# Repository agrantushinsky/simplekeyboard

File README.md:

# simplekeyboard: 60% Mechanical Keyboard PCB
## Overview
A custom 60% mechanical keyboard 2-layer PCB built around an STM32 microcontroller and USB-C connectivity. The design utilizes I2C IO expanders to simplify matrix trace routing across the board. 

## Current Status (WIP)
Hardware bring-up is actively underway. I identified an error that swapped the SCL and SDA lines on one of the IO expanders. The next step is performing a physical trace bodge to fix the bus so I can finish validating the matrix polling logic.

## Schematics

*View the full schematic PDF: [schematics.pdf](assets/schematics.pdf)*

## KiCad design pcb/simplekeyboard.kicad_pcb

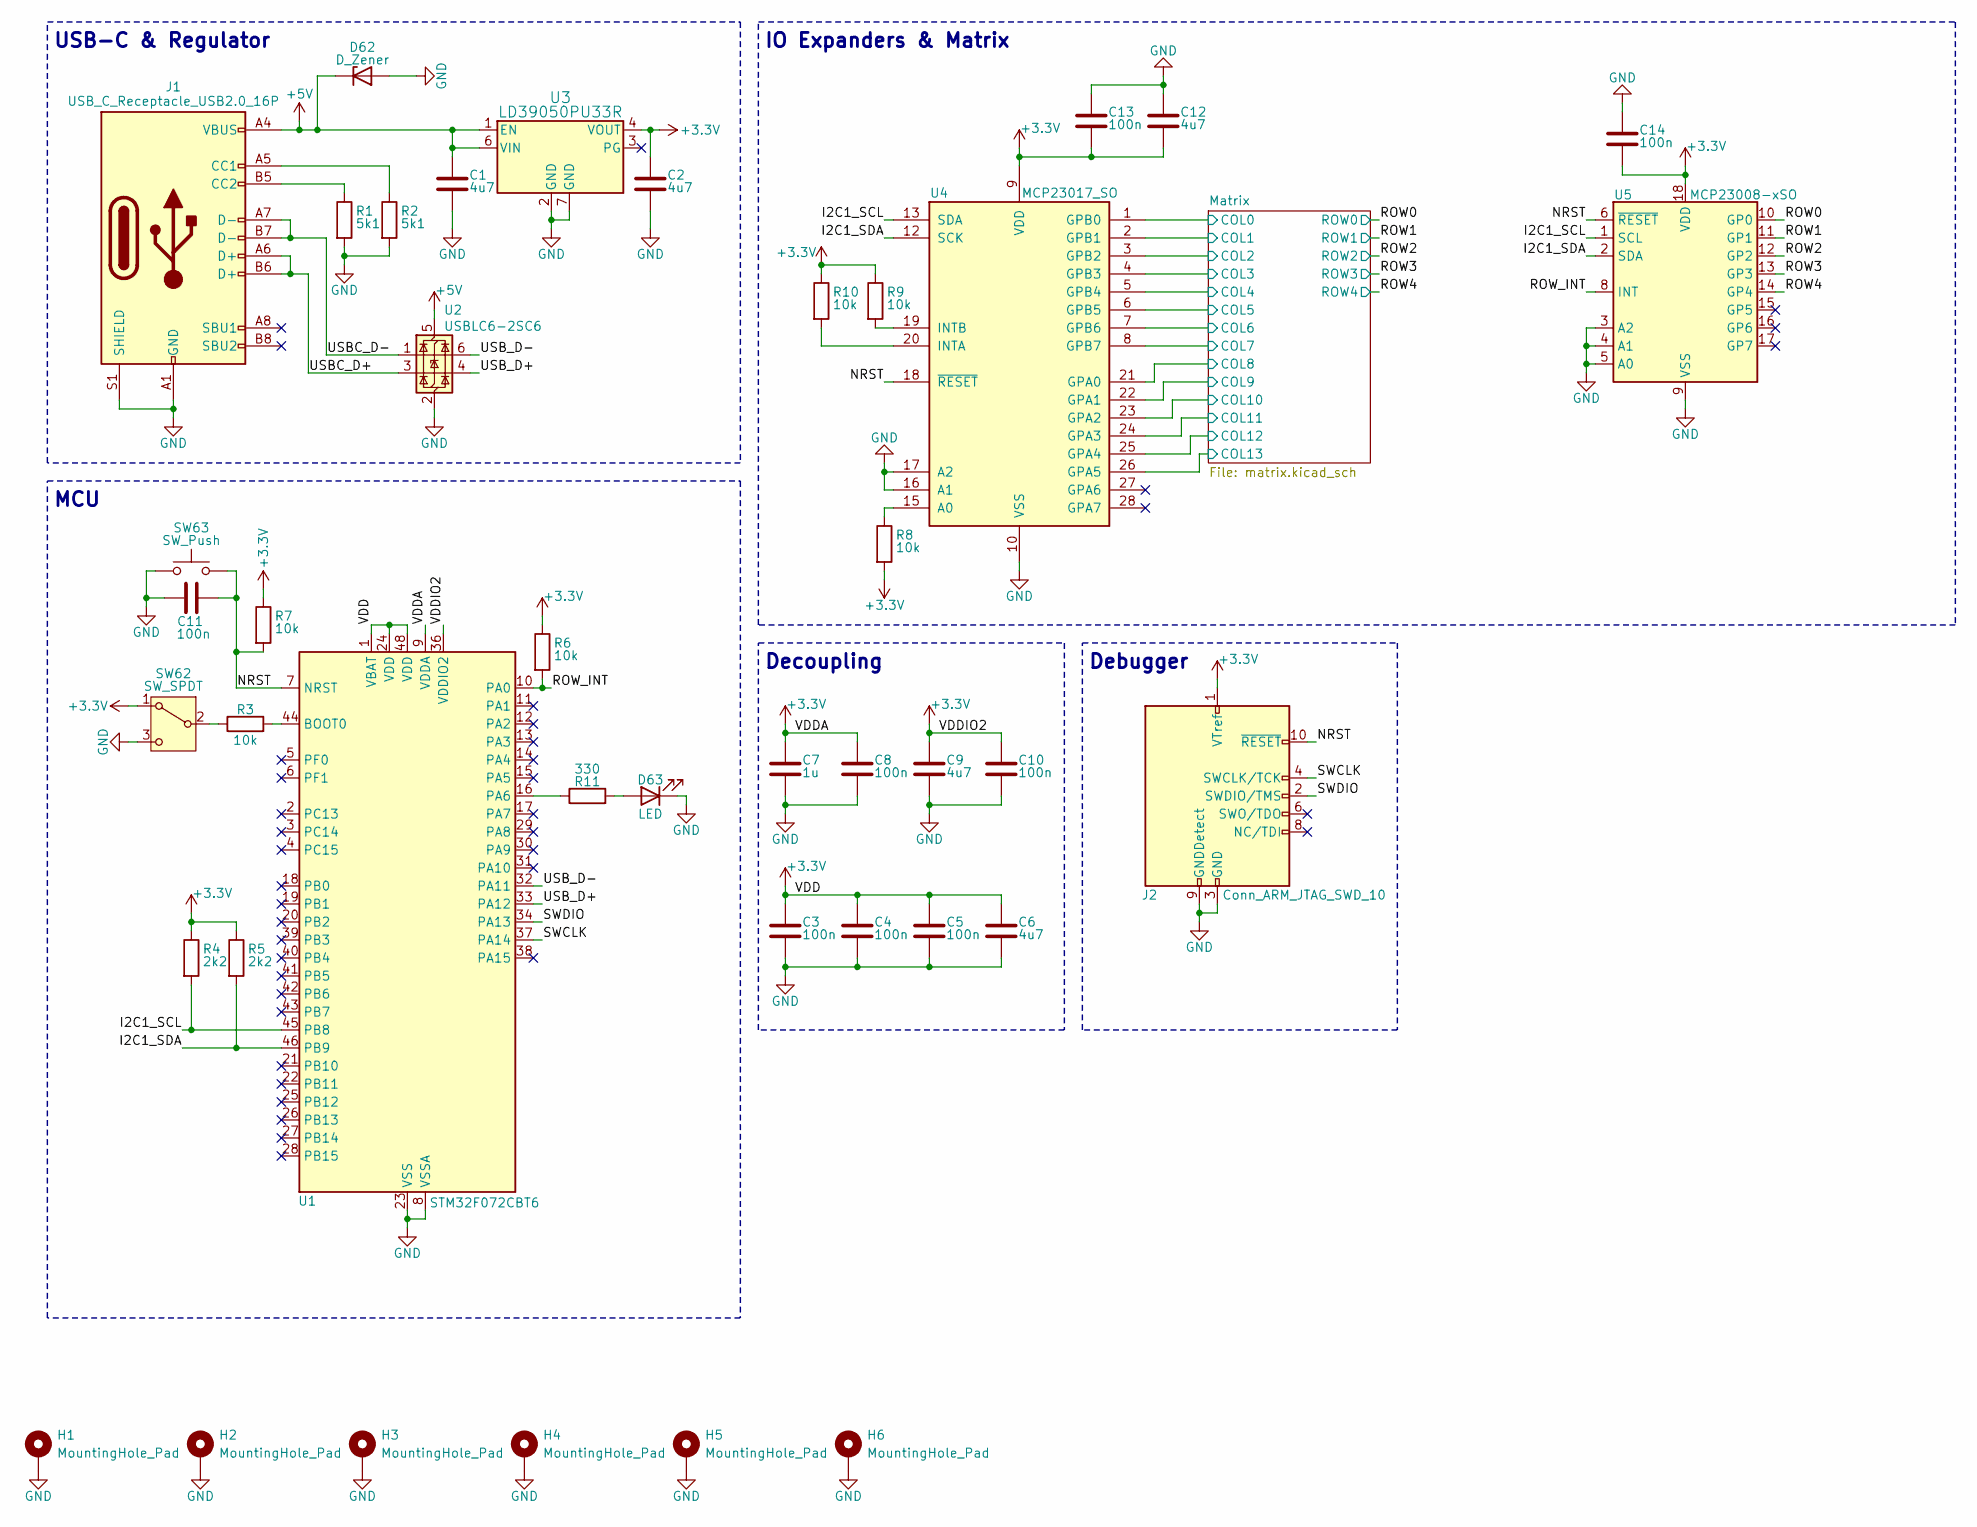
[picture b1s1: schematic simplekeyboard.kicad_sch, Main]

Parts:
C1, C2, C6, C9, C12: 4u7; C_0603_1608Metric
C3, C4, C5, C8, C10, C11, C13, C14: 100n; C_0402_1005Metric
C7: 1u; C_0603_1608Metric
D62: D_Zener; D_SOD-123
D63: LED; LED_0603_1608Metric
H1: MountingHole_Pad; 2.5mm
H2, H3, H4, H5, H6: MountingHole_Pad; 2.5mm_Oblong
J1: USB_C_Receptacle_USB2.0_16P; USB_C_Receptacle_HRO_TYPE-C-31-M-12
J2: Conn_ARM_JTAG_SWD_10; PinHeader_2x05_P1.27mm_Horizontal
R1, R2: 5k1; R_0603_1608Metric
R3, R6, R7, R8, R9, R10: 10k; R_0603_1608Metric
R4, R5: 2k2; R_0603_1608Metric
R11: 330; R_0603_1608Metric
SW62: SW_SPDT; SW_Slide_SPDT_Straight_CK_OS102011MS2Q
SW63: SW_Push; SW_PUSH_6mm
U1: STM32F072CBT6; LQFP-48_7x7mm_P0.5mm
U2: USBLC6-2SC6; SOT-23-6
U3: LD39050PU33R; DFN6_3X3_STM
U4: MCP23017_SO; SOIC-28W_7.5x17.9mm_P1.27mm
U5: MCP23008-xSO; SOIC-18W_7.5x11.6mm_P1.27mm

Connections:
+3.3V: C2.1, C3.1, C4.1, C5.1, C6.1, C7.1, C8.1, C9.1, C10.1, C12.2, C13.2, C14.2, J2.1 (VTref), R4.1, R5.1, R6.1, R7.1, R8.2, R9.1, R10.1, SW62.1 (A), U1.1 (VBAT), U1.9 (VDDA), U1.24 (VDD), U1.36 (VDDIO2), U1.48 (VDD), U3.4 (VOUT), U4.9 (VDD), U5.18 (VDD)
+5V: C1.1, D62.1 (K), J1.A4 (VBUS), J1.A9 (VBUS), J1.B4 (VBUS), J1.B9 (VBUS), U2.5 (VBUS), U3.1 (EN), U3.6 (VIN)
/I2C1_SCL: R4.2, U1.45 (PB8), U4.13 (SDA), U5.1 (SCL)
/I2C1_SDA: R5.2, U1.46 (PB9), U4.12 (SCK), U5.2 (SDA)
/Matrix/COL0: U4.1 (GPB0); also elsewhere on the board
/Matrix/COL1: U4.2 (GPB1); also elsewhere on the board
/Matrix/COL2: U4.3 (GPB2); also elsewhere on the board
/Matrix/COL3: U4.4 (GPB3); also elsewhere on the board
/Matrix/COL4: U4.5 (GPB4); also elsewhere on the board
/Matrix/COL5: U4.6 (GPB5); also elsewhere on the board
/Matrix/COL6: U4.7 (GPB6); also elsewhere on the board
/Matrix/COL7: U4.8 (GPB7); also elsewhere on the board
/Matrix/COL8: U4.21 (GPA0); also elsewhere on the board
/Matrix/COL9: U4.22 (GPA1); also elsewhere on the board
/Matrix/COL10: U4.23 (GPA2); also elsewhere on the board
/Matrix/COL11: U4.24 (GPA3); also elsewhere on the board
/Matrix/COL12: U4.25 (GPA4); also elsewhere on the board
/Matrix/COL13: U4.26 (GPA5); also elsewhere on the board
/NRST: C11.2, J2.10 (~RESET), R7.2, SW63.2, U1.7 (NRST), U4.18 (~RESET), U5.6 (~RESET)
/ROW0: U5.10 (GP0); also elsewhere on the board
/ROW1: U5.11 (GP1); also elsewhere on the board
/ROW2: U5.12 (GP2); also elsewhere on the board
/ROW3: U5.13 (GP3); also elsewhere on the board
/ROW4: U5.14 (GP4); also elsewhere on the board
/ROW_INT: R6.2, U1.10 (PA0), U5.8 (INT)
/SWCLK: J2.4 (SWCLK/TCK), U1.37 (PA14)
/SWDIO: J2.2 (SWDIO/TMS), U1.34 (PA13)
/USBC_D+: J1.A6 (D+), J1.B6 (D+), U2.3 (I/O2)
/USBC_D-: J1.A7 (D-), J1.B7 (D-), U2.1 (I/O1)
/USB_D+: U1.33 (PA12), U2.4 (I/O2)
/USB_D-: U1.32 (PA11), U2.6 (I/O1)
GND: C1.2, C2.2, C3.2, C4.2, C5.2, C6.2, C7.2, C8.2, C9.2, C10.2, C11.1, C12.1, C13.1, C14.1, D62.2 (A), D63.1 (K), H1.1, H2.1, H3.1, H4.1, H5.1, H6.1, J1.A1 (GND), J1.A12 (GND), J1.B1 (GND), J1.B12 (GND), J1.S1 (SHIELD), J2.3 (GND), J2.5 (GND), J2.9 (GNDDetect), R1.2, R2.2, SW62.3 (C), SW63.1, U1.8 (VSSA), U1.23 (VSS), U1.35 (VSS), U1.47 (VSS), U2.2 (GND), U3.2 (GND), U3.7 (GND), U4.10 (VSS), U4.16 (A1), U4.17 (A2), U5.3 (A2), U5.4 (A1), U5.5 (A0), U5.9 (VSS)
unnamed: D63.2 (A), R11.2
unnamed: J1.A5 (CC1), R2.1
unnamed: J1.B5 (CC2), R1.1
unnamed: R3.1, SW62.2 (B)
unnamed: R3.2, U1.44 (BOOT0)
unnamed: R11.1, U1.16 (PA6)
unnamed: R8.1, U4.15 (A0)
unnamed: R10.2, U4.20 (INTA)
unnamed: R9.2, U4.19 (INTB)

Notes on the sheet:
Decoupling
MCU
IO Expanders & Matrix
USB-C & Regulator
Debugger

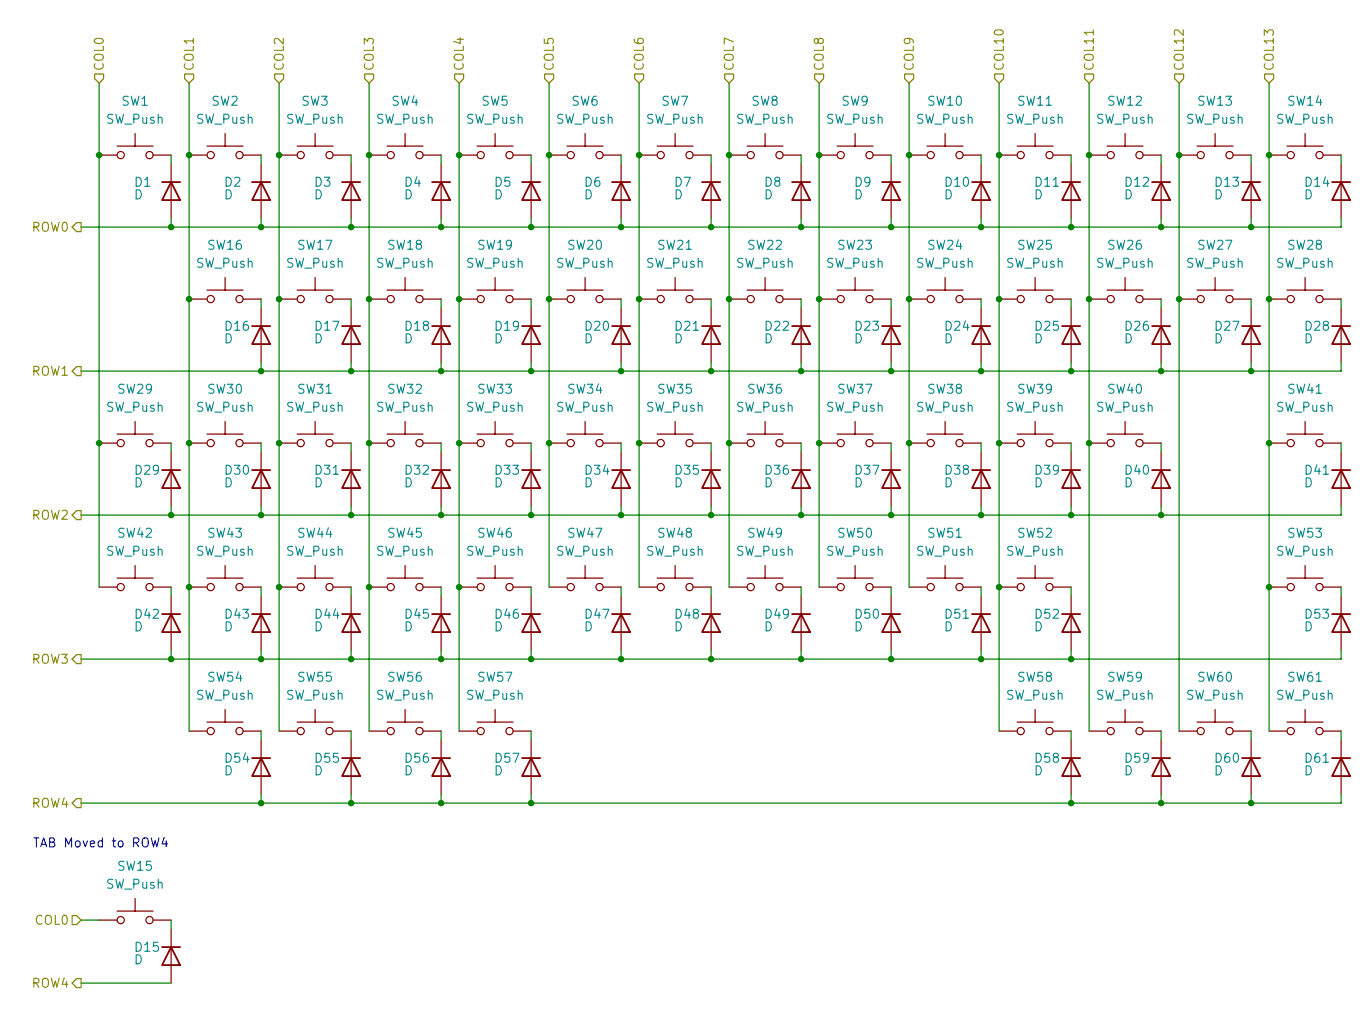
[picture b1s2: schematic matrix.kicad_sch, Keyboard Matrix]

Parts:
D1, D2, D3, D4, D5, D6, D7, D8, D9, D10, D11, D12, D13, D14, D15, D16, D17, D18, D19, D20, D21, D22, D23, D24, D25, D26, D27, D28, D29, D30, D31, D32, D33, D34, D35, D36, D37, D38, D39, D40, D41, D42, D43, D44, D45, D46, D47, D48, D49, D50, D51, D52, D53, D54, D55, D56, D57, D58, D59, D60, D61: D; D_SOD-123
SW1, SW2, SW3, SW4, SW5, SW6, SW7, SW8, SW9, SW10, SW11, SW12, SW13, SW16, SW17, SW18, SW19, SW20, SW21, SW22, SW23, SW24, SW25, SW26, SW27, SW30, SW31, SW32, SW33, SW34, SW35, SW36, SW37, SW38, SW39, SW40, SW43, SW44, SW45, SW46, SW47, SW48, SW49, SW50, SW51, SW52: SW_Push; MX-Solderable-1U
SW14: SW_Push; MX-Solderable-2U
SW15, SW28: SW_Push; MX-Solderable-1.5U
SW29: SW_Push; MX-Solderable-1.75U
SW41, SW42: SW_Push; MX-Solderable-2.25U
SW53: SW_Push; MX-Solderable-2.75U
SW54, SW55, SW56, SW58, SW59, SW60, SW61: SW_Push; MX-Solderable-1.25U
SW57: SW_Push; MX-Solderable-6.25U-ReversedStabilizers

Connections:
/Matrix/COL0: SW1.1, SW15.1, SW29.1, SW42.1; also elsewhere on the board
/Matrix/COL1: SW2.1, SW16.1, SW30.1, SW43.1, SW54.1; also elsewhere on the board
/Matrix/COL2: SW3.1, SW17.1, SW31.1, SW44.1, SW55.1; also elsewhere on the board
/Matrix/COL3: SW4.1, SW18.1, SW32.1, SW45.1, SW56.1; also elsewhere on the board
/Matrix/COL4: SW5.1, SW19.1, SW33.1, SW46.1, SW57.1; also elsewhere on the board
/Matrix/COL5: SW6.1, SW20.1, SW34.1, SW47.1; also elsewhere on the board
/Matrix/COL6: SW7.1, SW21.1, SW35.1, SW48.1; also elsewhere on the board
/Matrix/COL7: SW8.1, SW22.1, SW36.1, SW49.1; also elsewhere on the board
/Matrix/COL8: SW9.1, SW23.1, SW37.1, SW50.1; also elsewhere on the board
/Matrix/COL9: SW10.1, SW24.1, SW38.1, SW51.1; also elsewhere on the board
/Matrix/COL10: SW11.1, SW25.1, SW39.1, SW52.1, SW58.1; also elsewhere on the board
/Matrix/COL11: SW12.1, SW26.1, SW40.1, SW59.1; also elsewhere on the board
/Matrix/COL12: SW13.1, SW27.1, SW60.1; also elsewhere on the board
/Matrix/COL13: SW14.1, SW28.1, SW41.1, SW53.1, SW61.1; also elsewhere on the board
/ROW0: D1.2 (A), D2.2 (A), D3.2 (A), D4.2 (A), D5.2 (A), D6.2 (A), D7.2 (A), D8.2 (A), D9.2 (A), D10.2 (A), D11.2 (A), D12.2 (A), D13.2 (A), D14.2 (A); also elsewhere on the board
/ROW1: D16.2 (A), D17.2 (A), D18.2 (A), D19.2 (A), D20.2 (A), D21.2 (A), D22.2 (A), D23.2 (A), D24.2 (A), D25.2 (A), D26.2 (A), D27.2 (A), D28.2 (A); also elsewhere on the board
/ROW2: D29.2 (A), D30.2 (A), D31.2 (A), D32.2 (A), D33.2 (A), D34.2 (A), D35.2 (A), D36.2 (A), D37.2 (A), D38.2 (A), D39.2 (A), D40.2 (A), D41.2 (A); also elsewhere on the board
/ROW3: D42.2 (A), D43.2 (A), D44.2 (A), D45.2 (A), D46.2 (A), D47.2 (A), D48.2 (A), D49.2 (A), D50.2 (A), D51.2 (A), D52.2 (A), D53.2 (A); also elsewhere on the board
/ROW4: D15.2 (A), D54.2 (A), D55.2 (A), D56.2 (A), D57.2 (A), D58.2 (A), D59.2 (A), D60.2 (A), D61.2 (A); also elsewhere on the board
unnamed: D1.1 (K), SW1.2
unnamed: D2.1 (K), SW2.2
unnamed: D3.1 (K), SW3.2
unnamed: D4.1 (K), SW4.2
unnamed: D5.1 (K), SW5.2
unnamed: D6.1 (K), SW6.2
unnamed: D7.1 (K), SW7.2
unnamed: D8.1 (K), SW8.2
unnamed: D9.1 (K), SW9.2
unnamed: D10.1 (K), SW10.2
unnamed: D11.1 (K), SW11.2
unnamed: D12.1 (K), SW12.2
unnamed: D13.1 (K), SW13.2
unnamed: D14.1 (K), SW14.2
unnamed: D15.1 (K), SW15.2
unnamed: D16.1 (K), SW16.2
unnamed: D17.1 (K), SW17.2
unnamed: D18.1 (K), SW18.2
unnamed: D19.1 (K), SW19.2
unnamed: D20.1 (K), SW20.2
unnamed: D21.1 (K), SW21.2
unnamed: D22.1 (K), SW22.2
unnamed: D23.1 (K), SW23.2
unnamed: D24.1 (K), SW24.2
unnamed: D25.1 (K), SW25.2
unnamed: D26.1 (K), SW26.2
unnamed: D27.1 (K), SW27.2
unnamed: D28.1 (K), SW28.2
unnamed: D29.1 (K), SW29.2
unnamed: D30.1 (K), SW30.2
unnamed: D31.1 (K), SW31.2
unnamed: D32.1 (K), SW32.2
unnamed: D33.1 (K), SW33.2
unnamed: D34.1 (K), SW34.2
unnamed: D35.1 (K), SW35.2
unnamed: D36.1 (K), SW36.2
unnamed: D37.1 (K), SW37.2
unnamed: D38.1 (K), SW38.2
unnamed: D39.1 (K), SW39.2
unnamed: D40.1 (K), SW40.2
unnamed: D41.1 (K), SW41.2
unnamed: D42.1 (K), SW42.2
unnamed: D43.1 (K), SW43.2
unnamed: D44.1 (K), SW44.2
unnamed: D45.1 (K), SW45.2
unnamed: D46.1 (K), SW46.2
unnamed: D47.1 (K), SW47.2
unnamed: D48.1 (K), SW48.2
unnamed: D49.1 (K), SW49.2
unnamed: D50.1 (K), SW50.2
unnamed: D51.1 (K), SW51.2
unnamed: D52.1 (K), SW52.2
unnamed: D53.1 (K), SW53.2
unnamed: D54.1 (K), SW54.2
unnamed: D55.1 (K), SW55.2
unnamed: D56.1 (K), SW56.2
unnamed: D57.1 (K), SW57.2
unnamed: D58.1 (K), SW58.2
unnamed: D59.1 (K), SW59.2
unnamed: D60.1 (K), SW60.2
unnamed: D61.1 (K), SW61.2

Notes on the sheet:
TAB Moved to ROW4

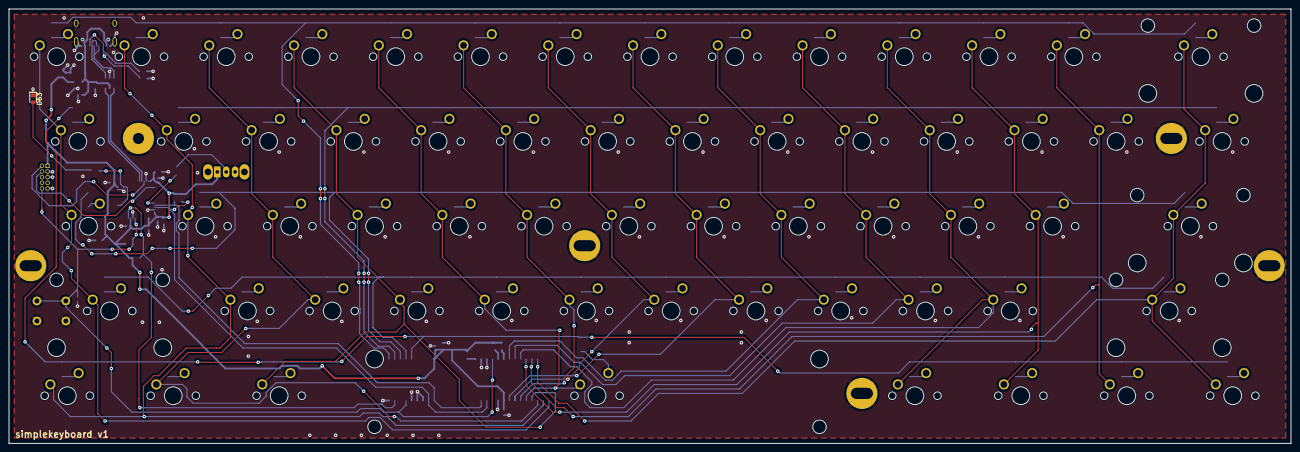
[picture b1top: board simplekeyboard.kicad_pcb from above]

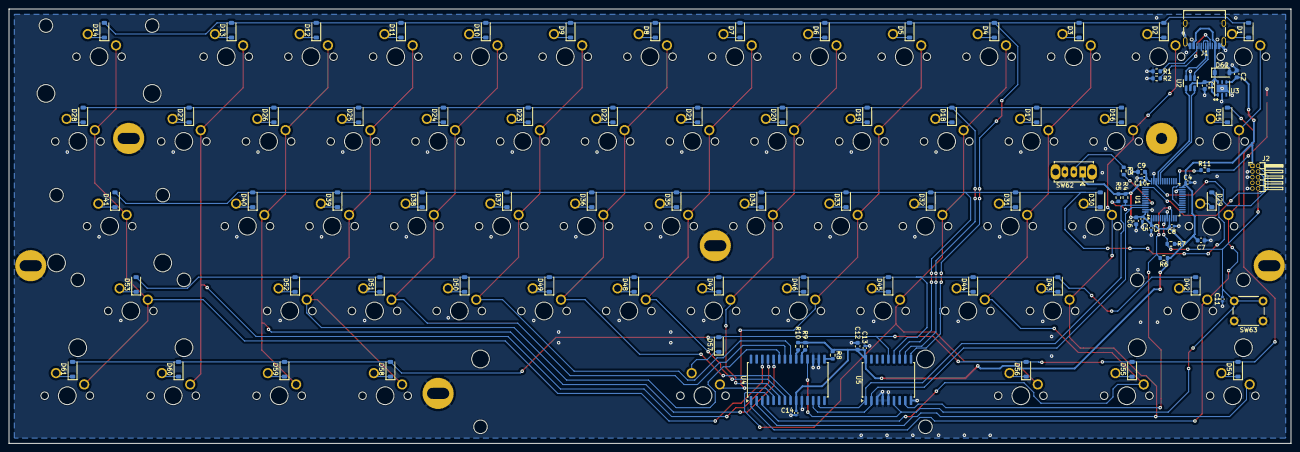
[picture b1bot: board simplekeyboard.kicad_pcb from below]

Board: 2 copper layers, 288.1 x 97.6 mm, 164 parts (96 on the bottom side), 102 nets.

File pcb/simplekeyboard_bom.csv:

Reference,Qty,Value,DNP,Exclude from BOM,Exclude from Board,Footprint,Datasheet,Manufacturer Part  Number
"C1,C2,C6,C9,C12",5,4u7,,,,Capacitor_SMD:C_0603_1608Metric,~,GRM188R61E475KE11D
"C3,C4,C5,C8,C10,C11,C13,C14",8,100n,,,,Capacitor_SMD:C_0402_1005Metric,~,GCM155R71H104KE02D
C7,1,1u,,,,Capacitor_SMD:C_0603_1608Metric,~,GCM188R71E105KA64J
"D1,D2,D3,D4,D5,D6,D7,D8,D9,D10,D11,D12,D13,D14,D15,D16,D17,D18,D19,D20,D21,D22,D23,D24,D25,D26,D27,D28,D29,D30,D31,D32,D33,D34,D35,D36,D37,D38,D39,D40,D41,D42,D43,D44,D45,D46,D47,D48,D49,D50,D51,D52,D53,D54,D55,D56,D57,D58,D59,D60,D61",61,D,,,,Diode_SMD:D_SOD-123,~,1N4148W-TP
D62,1,D_Zener,,,,Diode_SMD:D_SOD-123,~,MMSZ5233BT1G
D63,1,LED,,,,LED_SMD:LED_0603_1608Metric,~,LTST-C191KFKT
H1,10,MountingHole_Pad,,Excluded from BOM,,Keyboard_Mounts:2.5mm,~,50M020040P008B
"H2,H3,H4,H5,H6",10,MountingHole_Pad,,Excluded from BOM,,Keyboard_Mounts:2.5mm_Oblong,~,50M020040P006B
J1,1,USB_C_Receptacle_USB2.0_16P,,,,Connector_USB:USB_C_Receptacle_HRO_TYPE-C-31-M-12,https://www.usb.org/sites/default/files/documents/usb_type-c.zip,UJ20-C-H-G-SMT-2A-P16-TR
J2,1,Conn_ARM_JTAG_SWD_10,,,,Connector_PinHeader_1.27mm:PinHeader_2x05_P1.27mm_Horizontal,http://infocenter.arm.com/help/topic/com.arm.doc.ddi0314h/DD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,FTSH-105-01-F-D-RA
"R1,R2",2,5k1,,,,Resistor_SMD:R_0603_1608Metric,~,RC0603FR-075K1L
"R3,R6,R7,R8,R9,R10",6,10k,,,,Resistor_SMD:R_0603_1608Metric,~,RC0603FR-0710KL
"R4,R5",2,2k2,,,,Resistor_SMD:R_0603_1608Metric,~,RC0603FR-072K2L
R11,1,330,,,,Resistor_SMD:R_0603_1608Metric,~,RC0603FR-07330RL
"SW1,SW2,SW3,SW4,SW5,SW6,SW7,SW8,SW9,SW10,SW11,SW12,SW13,SW16,SW17,SW18,SW19,SW20,SW21,SW22,SW23,SW24,SW25,SW26,SW27,SW30,SW31,SW32,SW33,SW34,SW35,SW36,SW37,SW38,SW39,SW40,SW43,SW44,SW45,SW46,SW47,SW48,SW49,SW50,SW51,SW52",46,SW_Push,,,,ai03_MX:MX-Solderable-1U,~,
SW14,1,SW_Push,,,,ai03_MX:MX-Solderable-2U,~,
"SW15,SW28",2,SW_Push,,,,ai03_MX:MX-Solderable-1.5U,~,
SW29,1,SW_Push,,,,ai03_MX:MX-Solderable-1.75U,~,
"SW41,SW42",2,SW_Push,,,,ai03_MX:MX-Solderable-2.25U,~,
SW53,1,SW_Push,,,,ai03_MX:MX-Solderable-2.75U,~,
"SW54,SW55,SW56,SW58,SW59,SW60,SW61",7,SW_Push,,,,ai03_MX:MX-Solderable-1.25U,~,
SW57,1,SW_Push,,,,ai03_MX:MX-Solderable-6.25U,~,
SW62,1,SW_SPDT,,,,Button_Switch_THT:SW_Slide_SPDT_Straight_CK_OS102011MS2Q,~,OS102011MS2QN1
SW63,1,SW_Push,,,,Button_Switch_THT:SW_PUSH_6mm,~,PTS645SL50-2 LFS
U1,1,STM32F072CBT6,,,,Package_QFP:LQFP-48_7x7mm_P0.5mm,https://www.st.com/resource/en/datasheet/stm32f072cb.pdf,STM32F072CBT6
U2,1,USBLC6-2SC6,,,,Package_TO_SOT_SMD:SOT-23-6,https://www.st.com/resource/en/datasheet/usblc6-2.pdf,USBLC6-2SC6
U3,1,LD39050PU33R,,,,Keyboard_Power:DFN6_3X3_STM,https://www.st.com/resource/en/datasheet/ld39050.pdf,LD39050PU33R
U4,1,MCP23017_SO,,,,Package_SO:SOIC-28W_7.5x17.9mm_P1.27mm,https://ww1.microchip.com/downloads/aemDocuments/documents/A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,MCP23017T-E/SO
U5,1,MCP23008-xSO,,,,Package_SO:SOIC-18W_7.5x11.6mm_P1.27mm,http://ww1.microchip.com/downloads/en/DeviceDoc/MCP23008-MCP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,MCP23008T-E/SO

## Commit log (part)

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2025-12-19 Create project
2025-12-20 Complete matrix and start MCU
2026-01-09 Complete MCU USB and power
2026-01-09 Add reset and boot
2026-01-10 Finish board schematic
2026-01-10 Add LICENSE
2026-01-10 Start PCB layout
2026-01-10 Almost done PCB
2026-01-11 Matrix routing is a disaster
2026-01-11 Route diodes
2026-02-01 IO expanders in schematic
2026-02-01 Fix I2C bus
2026-02-01 Reverse diodes on keyboard matrix
2026-05-06 Finish and validate schematic
2026-06-19 Clear board and add mounting holes
2026-06-20 Routing almost complete
2026-06-24 Finished routing and various fixes
